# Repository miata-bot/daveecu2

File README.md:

# DaveECU2 Speeduino Mainboard

## Features

* 4 Injectors
* 4 Ignitions
* 1 each CAM and Crank input
* 1 wire Idle
* PWM boost
* AC control
* 4 additional high current outputs
* SD card for logginglogging
* [PLANNED] RTC w/ battery backup

## Schematic TODO

* Calculate R53 and R54 values for 3v3 rail
* ~~Convert all resistors in the sensor sheet to 0402~~ have to hand solder so don't want that small
* ~~Convert all capacitors in the sensor sheet to 0402~~ have to hand solder so don't want that small
* Condense common resistors into common values
* Condense common caps into common values
* ~~Find a USB-C connector~~ Replaced with USB Type B "printer" connector
* Check if Q1 and Q2 can be the same part

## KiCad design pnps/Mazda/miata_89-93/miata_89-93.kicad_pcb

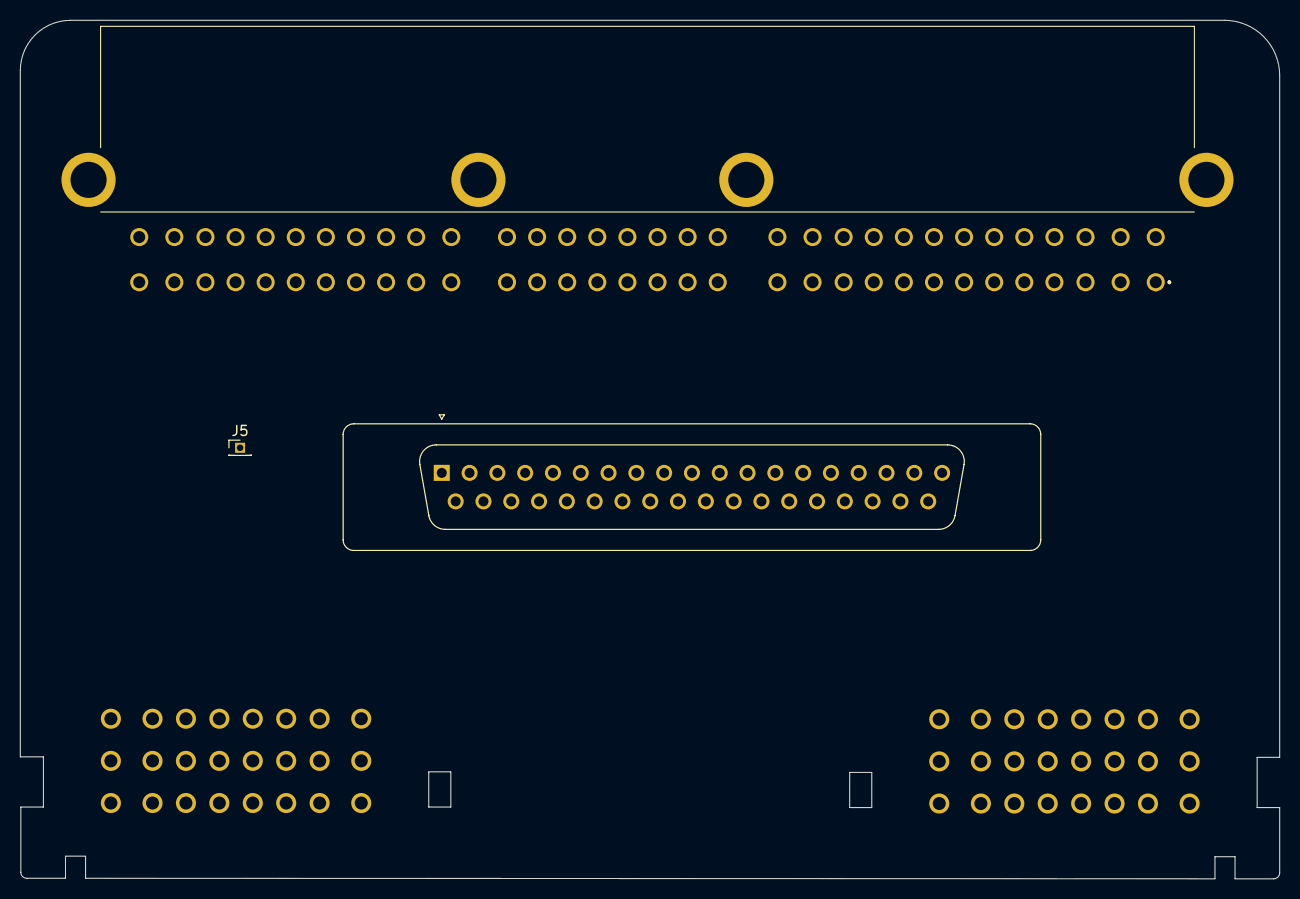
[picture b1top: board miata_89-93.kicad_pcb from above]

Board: 2 copper layers, 125.5 x 85.5 mm, 5 parts (0 on the bottom side), 24 nets.

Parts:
J1: 174518-7
J2: Conn_01x37; DSUB-37_Male_Vertical_P2.77x2.84mm
J3: CONN_BLACK; Delphi_Sicma_24_Black
J4: CONN_GRAY; Delphi_Sicma_24_Grey
J5: 2ND TRIGGER; PinHeader_1x01_P1.27mm_Vertical

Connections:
GND: J1.MH1, J1.MH2, J1.MH3, J1.MH4, J3.A1, J3.A3, J3.A4, J3.A5, J3.B1, J3.B2, J3.B3, J3.B4, J4.C1, J4.C2
MIATA_1B: J1.16, J2.28
MIATA_1E: J1.56, J4.B4
MIATA_1G: J1.55, J3.C1
MIATA_1H: J1.63, J3.C3
MIATA_1N: J1.52, J1.60, J2.26, J3.A7
MIATA_1Q: J1.50, J4.A1
MIATA_1R: J1.58, J4.C4
MIATA_1V: J1.12, J4.A2
MIATA_2A: J1.8, J2.8, J2.9
MIATA_2C: J1.7, J2.1
MIATA_2D: J1.9, J2.2
MIATA_2E: J1.24, J2.24, J4.A8
MIATA_2G: J1.23, J4.A7, J5.1
MIATA_2I: J1.22, J4.C5
MIATA_2K: J1.21, J4.B8
MIATA_2L: J1.29, J2.22, J4.A3
MIATA_2N: J1.28, J2.23
MIATA_2O: J1.19, J2.37, J4.C3
MIATA_2P: J1.27, J2.20, J4.A4
MIATA_2Q: J1.18, J2.21, J4.A5
MIATA_2U: J1.3, J3.C7
MIATA_2V: J1.6, J3.C5
MIATA_2W: J1.2, J4.B7

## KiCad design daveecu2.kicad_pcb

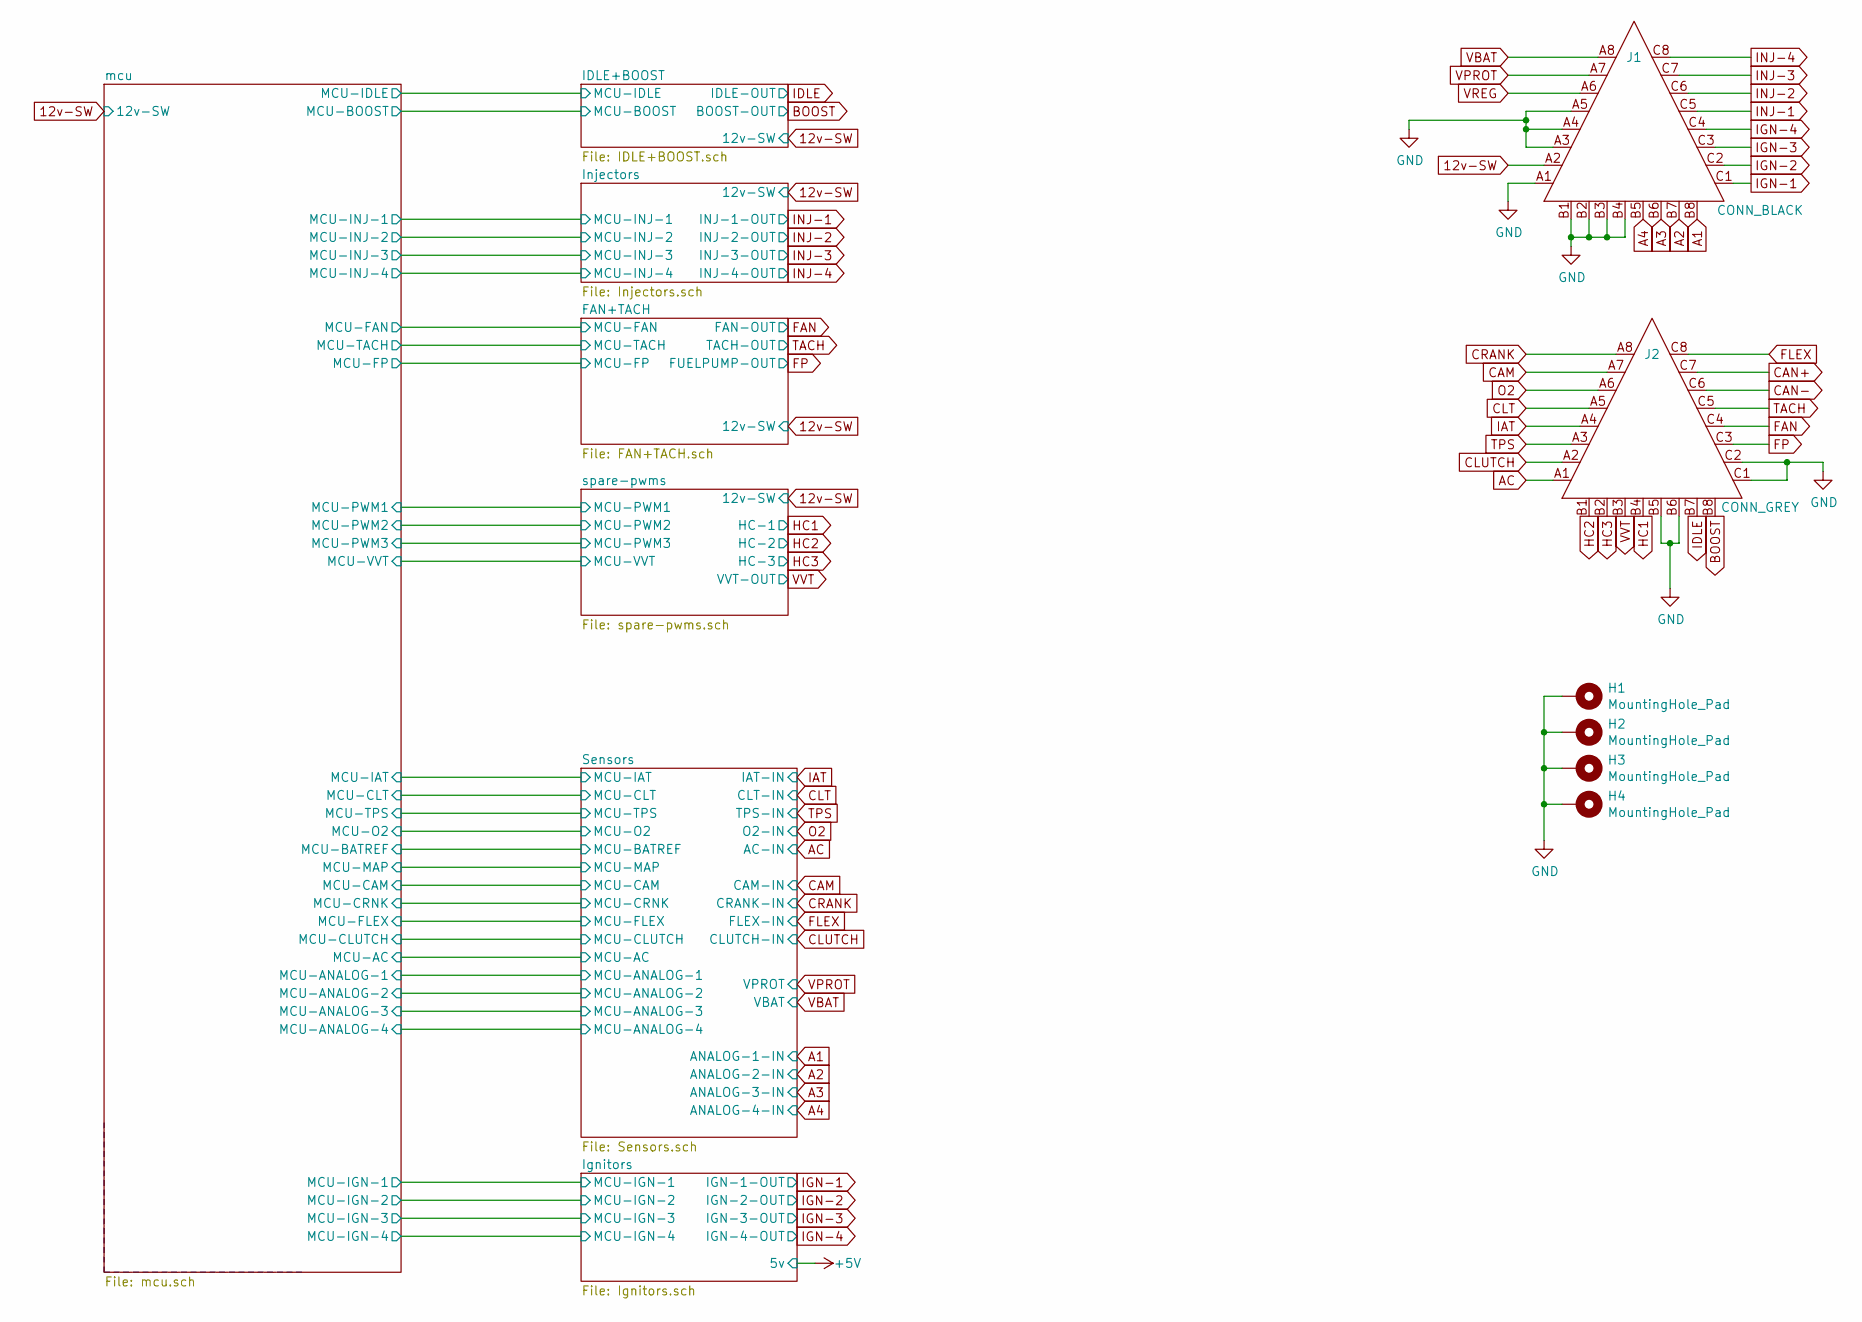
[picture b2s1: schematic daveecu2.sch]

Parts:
H1, H2, H3, H4: MountingHole_Pad; MountingHole_4.3mm_M4_Pad_Via
J1: CONN_BLACK; Delphi_Sicma_24_Black
J2: CONN_GREY; Delphi_Sicma_24_Grey

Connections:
12v-SW: J1.A2; also elsewhere on the board
A1: J1.B8; also elsewhere on the board
A2: J1.B7; also elsewhere on the board
A3: J1.B6; also elsewhere on the board
A4: J1.B5; also elsewhere on the board
AC: J2.A1; also elsewhere on the board
ADC-CLAMP-7: J2.C8; also elsewhere on the board
BOOST: J2.B8; also elsewhere on the board
CAM: J2.A7; also elsewhere on the board
CAN+: J2.C7; also elsewhere on the board
CAN-: J2.C6; also elsewhere on the board
CLT: J2.A5; also elsewhere on the board
CLUTCH: J2.A2; also elsewhere on the board
CRANK: J2.A8; also elsewhere on the board
FAN: J2.C4; also elsewhere on the board
FP: J2.C3; also elsewhere on the board
GND: H1.1, H2.1, H3.1, H4.1, J1.A1, J1.A3, J1.A4, J1.A5, J1.B1, J1.B2, J1.B3, J1.B4, J2.B5, J2.B6, J2.C1, J2.C2; also elsewhere on the board
HC1: J2.B4; also elsewhere on the board
HC2: J2.B1; also elsewhere on the board
HC3: J2.B2; also elsewhere on the board
IAT: J2.A4; also elsewhere on the board
IDLE: J2.B7; also elsewhere on the board
IGN-1: J1.C1; also elsewhere on the board
IGN-2: J1.C2; also elsewhere on the board
IGN-3: J1.C3; also elsewhere on the board
IGN-4: J1.C4; also elsewhere on the board
INJ-1: J1.C5; also elsewhere on the board
INJ-2: J1.C6; also elsewhere on the board
INJ-3: J1.C7; also elsewhere on the board
INJ-4: J1.C8; also elsewhere on the board
O2: J2.A6; also elsewhere on the board
TACH: J2.C5; also elsewhere on the board
TPS: J2.A3; also elsewhere on the board
VBAT: J1.A8; also elsewhere on the board
VPROT: J1.A7; also elsewhere on the board
VREG: J1.A6; also elsewhere on the board
VVT: J2.B3; also elsewhere on the board

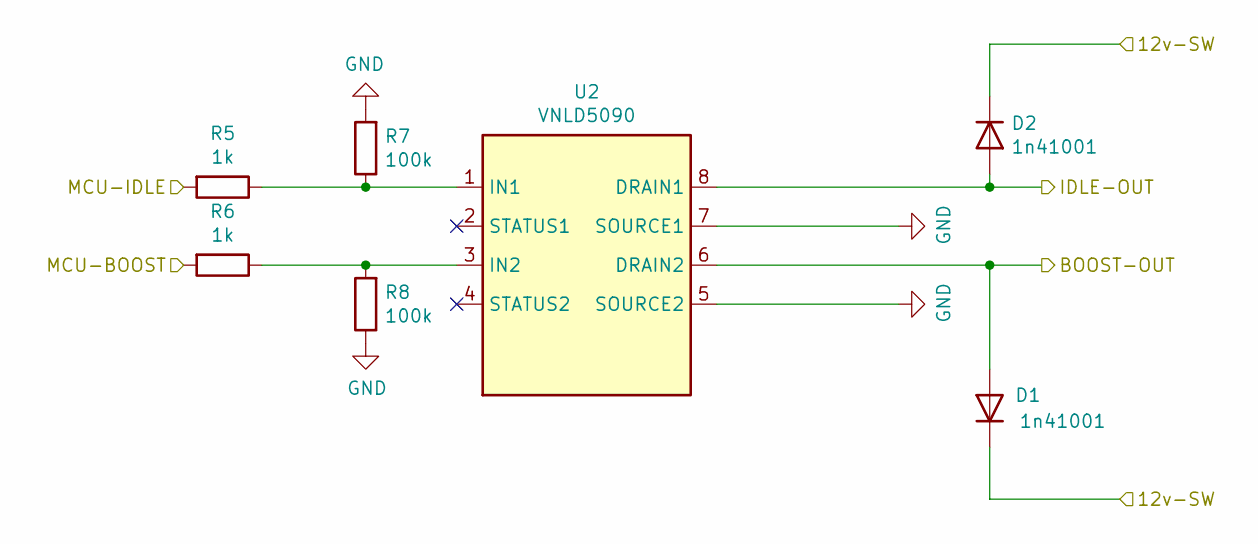
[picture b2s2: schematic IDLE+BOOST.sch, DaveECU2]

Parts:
D1, D2: 1n41001; D_SOD-123; LCSC_PN C162732
R5, R6: 1k; R_0603_1608Metric_Pad0.98x0.95mm_HandSolder; DIGIKEY 311-1.00KCRCT-ND
R7, R8: 100k; R_0603_1608Metric_Pad0.98x0.95mm_HandSolder; DIGIKEY 311-100KCRCT-ND
U2: VNLD5090; SOIC-8_3.9x4.9mm_P1.27mm

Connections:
12v-SW: D1.1 (K), D2.1 (K); also elsewhere on the board
/IDLE+BOOST/MCU-BOOST: R6.2; also elsewhere on the board
/IDLE+BOOST/MCU-IDLE: R5.2; also elsewhere on the board
BOOST: D1.2 (A), U2.6 (DRAIN2); also elsewhere on the board
GND: R7.2, R8.1, U2.5 (SOURCE2), U2.7 (SOURCE1); also elsewhere on the board
IDLE: D2.2 (A), U2.8 (DRAIN1); also elsewhere on the board
unnamed: R5.1, R7.1, U2.1 (IN1)
unnamed: R6.1, R8.2, U2.3 (IN2)

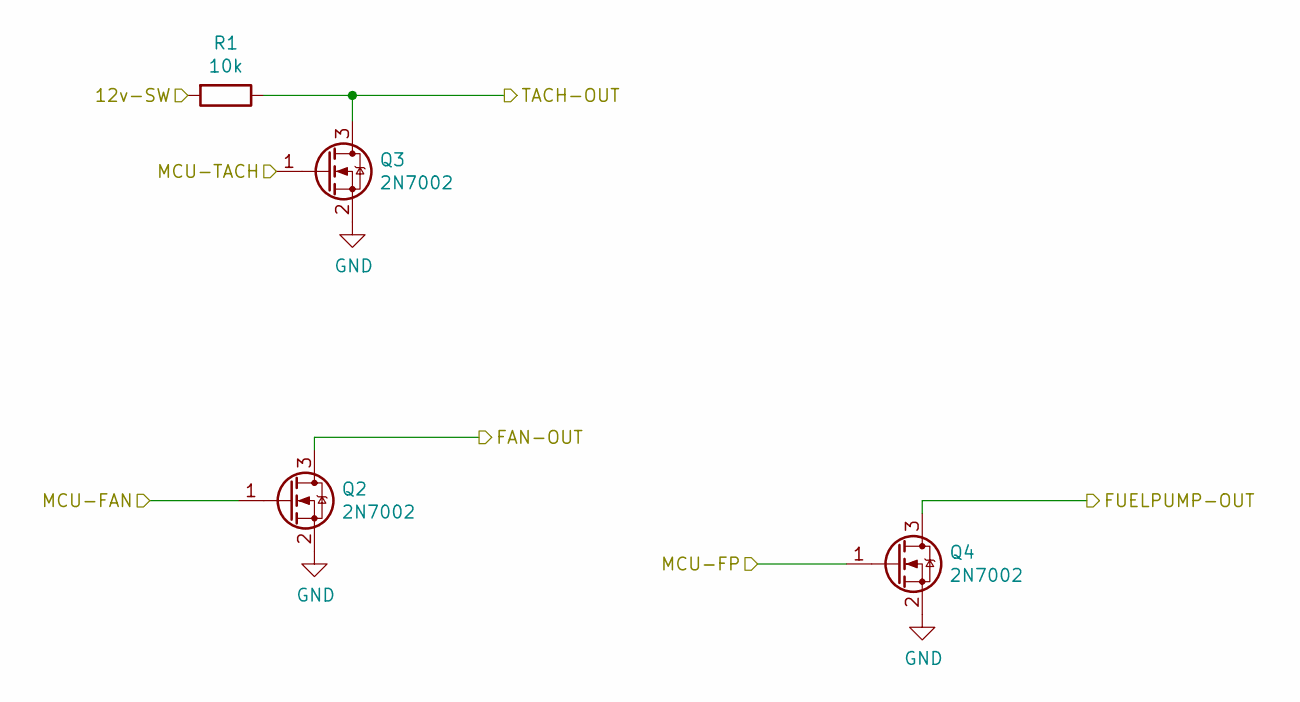
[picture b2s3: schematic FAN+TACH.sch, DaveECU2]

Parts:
Q2, Q3, Q4: 2N7002; SOT-23
R1: 10k; R_0603_1608Metric_Pad0.98x0.95mm_HandSolder; DIGIKEY 311-1.00KCRCT-ND

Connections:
12v-SW: R1.2; also elsewhere on the board
/FAN+TACH/MCU-FAN: Q2.1 (G); also elsewhere on the board
/FAN+TACH/MCU-FP: Q4.1 (G); also elsewhere on the board
/FAN+TACH/MCU-TACH: Q3.1 (G); also elsewhere on the board
FAN: Q2.3 (D); also elsewhere on the board
FP: Q4.3 (D); also elsewhere on the board
GND: Q2.2 (S), Q3.2 (S), Q4.2 (S); also elsewhere on the board
TACH: Q3.3 (D), R1.1; also elsewhere on the board

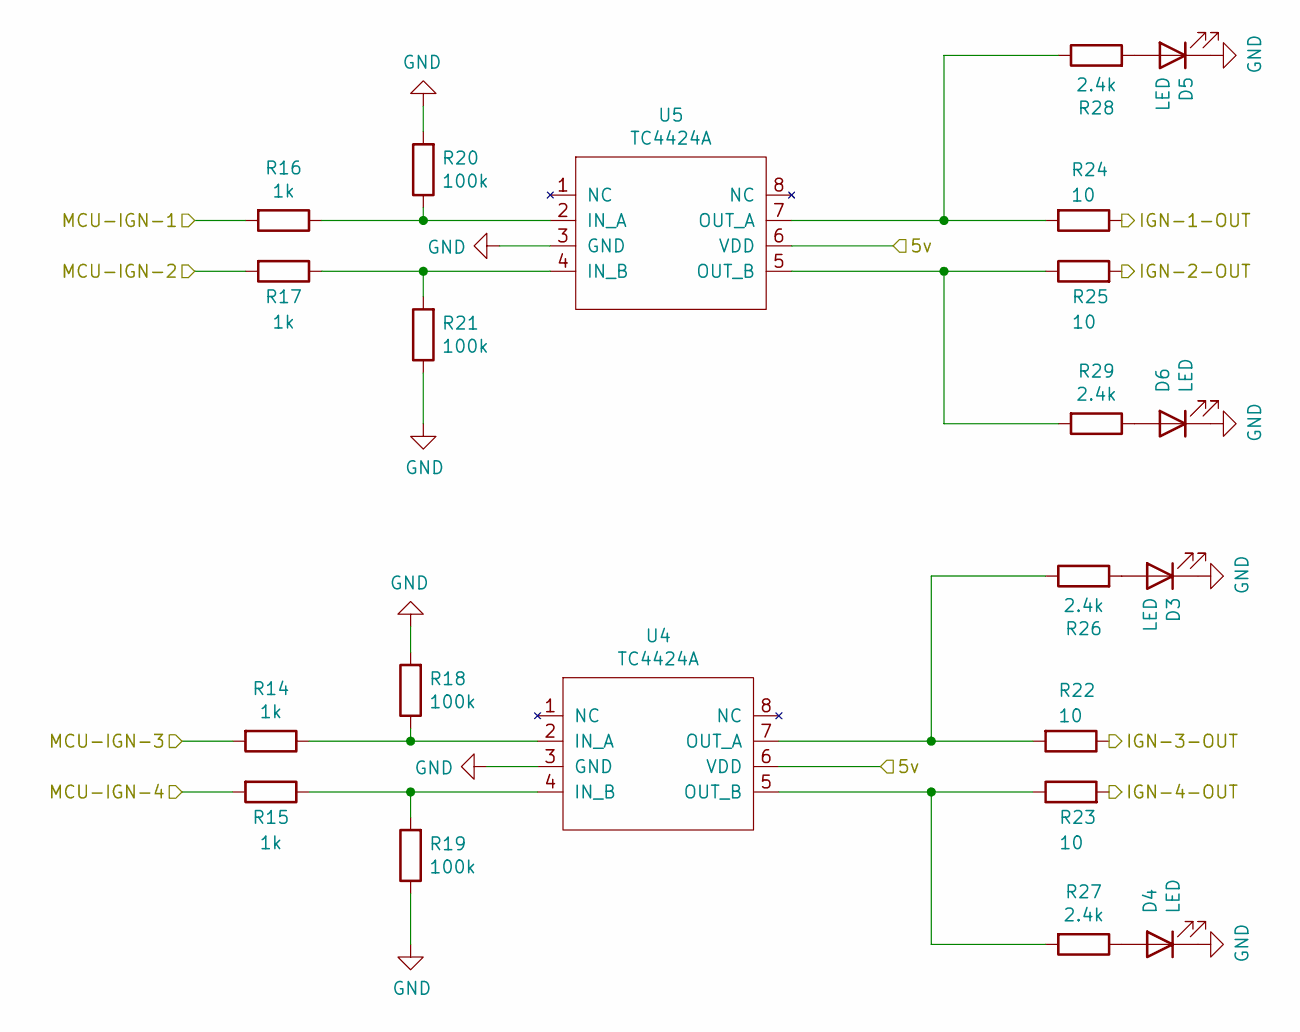
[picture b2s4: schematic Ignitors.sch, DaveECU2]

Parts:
D3, D4, D5, D6: LED; LED_0603_1608Metric_Pad1.05x0.95mm_HandSolder
R14, R15, R16, R17: 1k; R_0603_1608Metric_Pad0.98x0.95mm_HandSolder; DIGIKEY 311-1.00KCRCT-ND
R18, R19, R20, R21: 100k; R_0603_1608Metric_Pad0.98x0.95mm_HandSolder; DIGIKEY 311-100KCRCT-ND
R22, R23, R24, R25: 10; R_0603_1608Metric_Pad0.98x0.95mm_HandSolder; DIGIKEY 311-10.0CRCT-ND
R26, R27, R28, R29: 2.4k; R_0603_1608Metric_Pad0.98x0.95mm_HandSolder; DIGIKEY 311-2.40KCRCT-ND
U4, U5: TC4424A; SOIC-8_3.9x4.9mm_P1.27mm; DIGIKEY TC4424AVOA-ND

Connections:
/Ignitors/MCU-IGN-1: R16.2; also elsewhere on the board
/Ignitors/MCU-IGN-2: R17.2; also elsewhere on the board
/Ignitors/MCU-IGN-3: R14.2; also elsewhere on the board
/Ignitors/MCU-IGN-4: R15.2; also elsewhere on the board
GND: D3.1 (K), D4.1 (K), D5.1 (K), D6.1 (K), R18.2, R19.1, R20.2, R21.1, U4.3 (GND), U5.3 (GND); also elsewhere on the board
IGN-1: R24.1; also elsewhere on the board
IGN-2: R25.2; also elsewhere on the board
IGN-3: R22.1; also elsewhere on the board
IGN-4: R23.2; also elsewhere on the board
unnamed: D3.2 (A), R26.2
unnamed: D4.2 (A), R27.1
unnamed: D5.2 (A), R28.2
unnamed: D6.2 (A), R29.1
unnamed: R14.1, R18.1, U4.2 (IN_A)
unnamed: R15.1, R19.2, U4.4 (IN_B)
unnamed: R16.1, R20.1, U5.2 (IN_A)
unnamed: R17.1, R21.2, U5.4 (IN_B)
unnamed: R22.2, R26.1, U4.7 (OUT_A)
unnamed: R23.1, R27.2, U4.5 (OUT_B)
unnamed: R24.2, R28.1, U5.7 (OUT_A)
unnamed: R25.1, R29.2, U5.5 (OUT_B)
VPROT: U4.6 (VDD), U5.6 (VDD); also elsewhere on the board

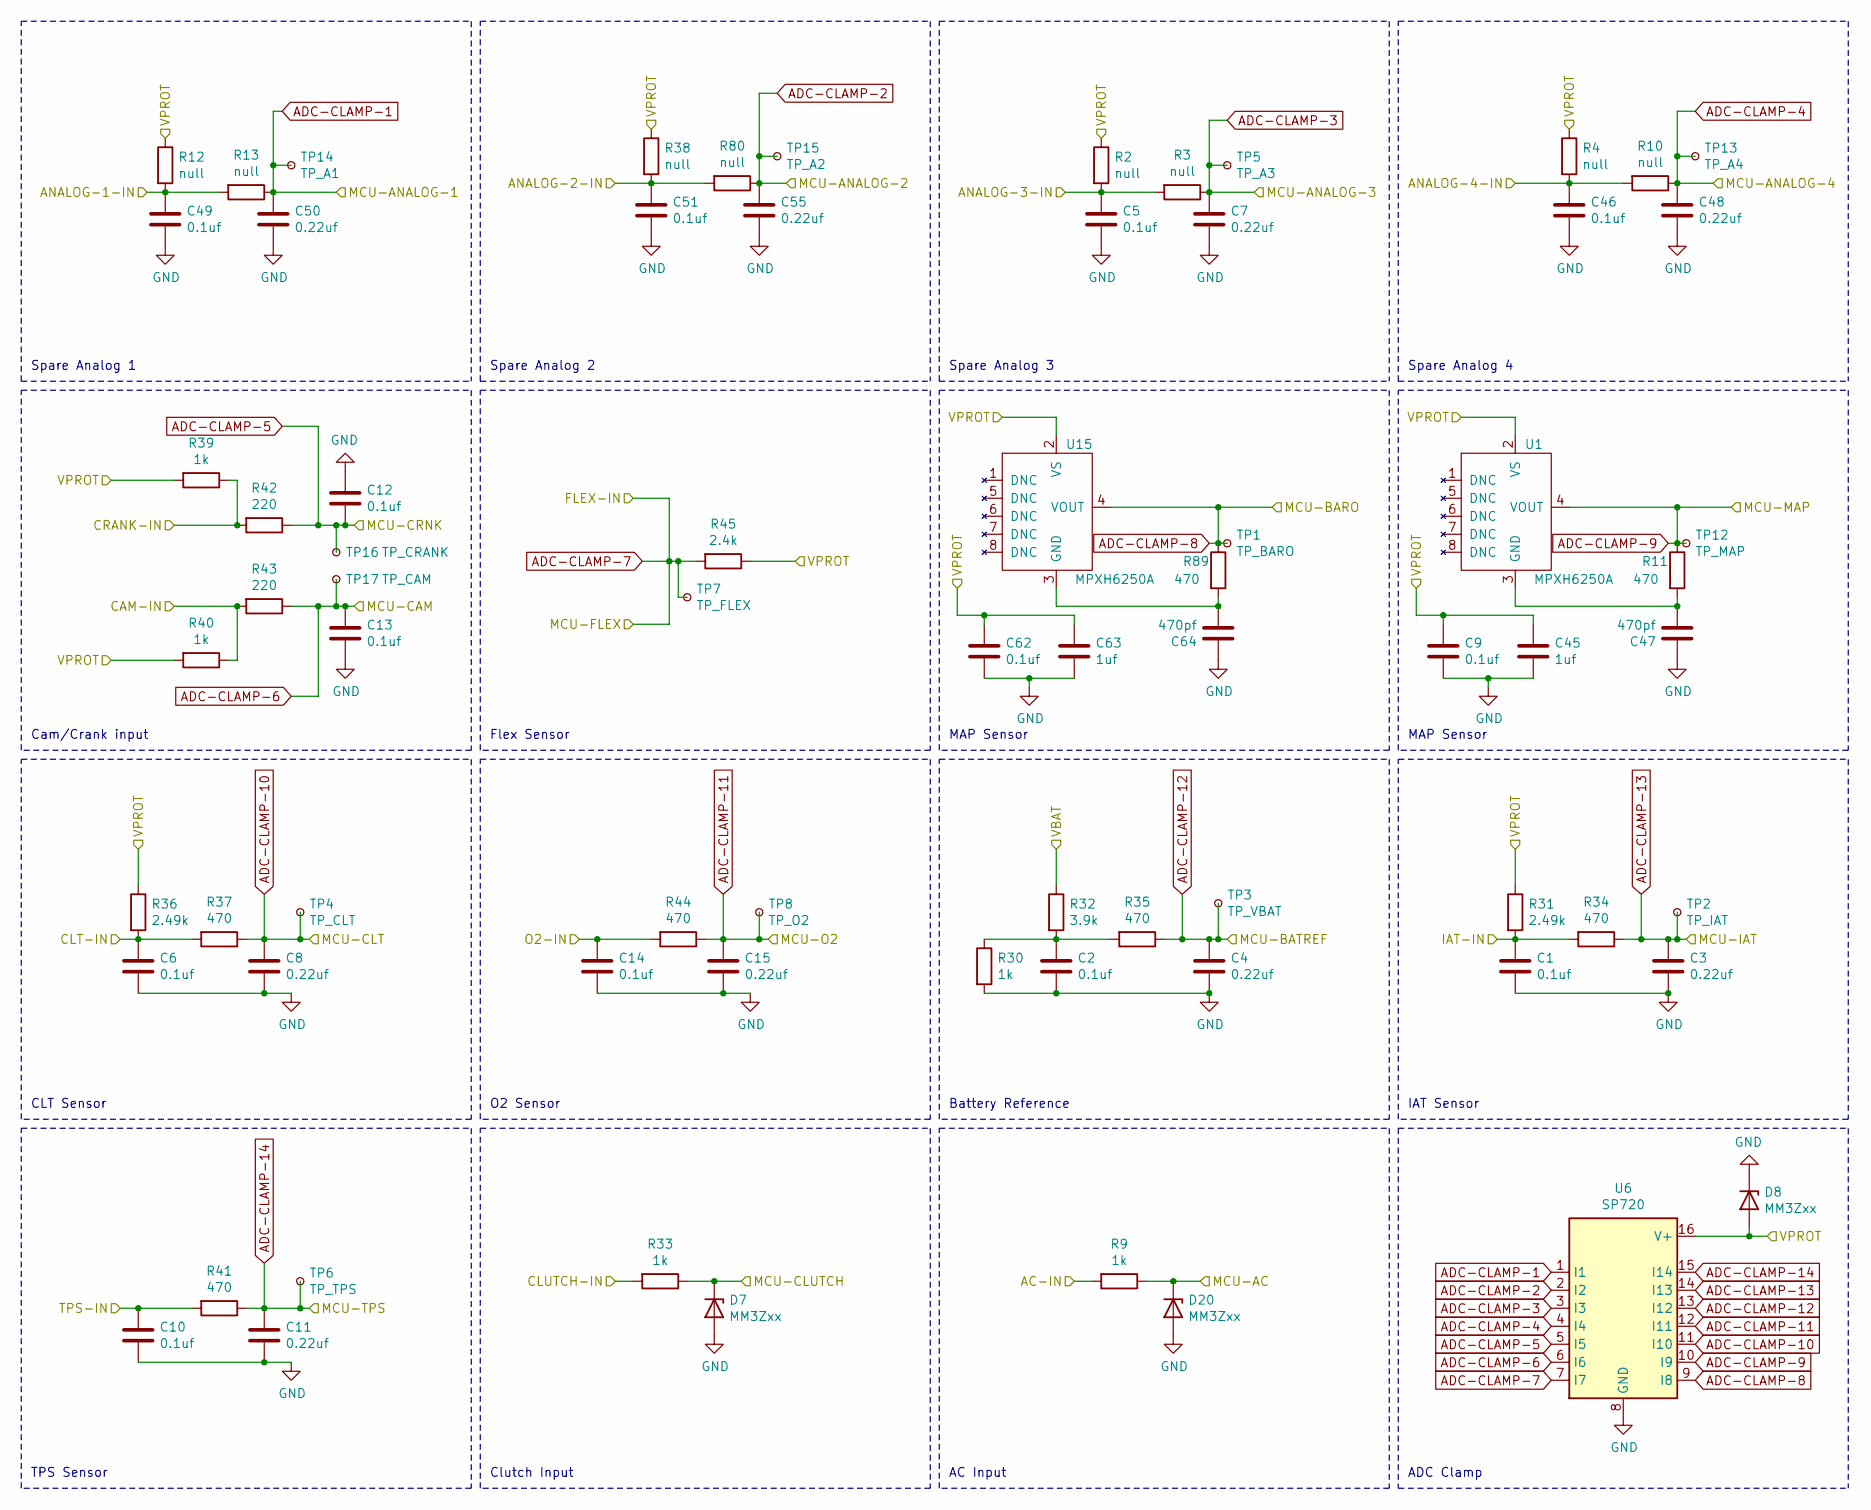
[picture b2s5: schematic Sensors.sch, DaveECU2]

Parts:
C1, C2, C5, C6, C9, C10, C12, C13, C14, C46, C49, C51, C62: 0.1uf; C_0805_2012Metric_Pad1.18x1.45mm_HandSolder; DIGIKEY 311-1140-1-ND
C3, C4, C7, C8, C11, C15, C48, C50, C55: 0.22uf; C_0805_2012Metric_Pad1.18x1.45mm_HandSolder; DIGIKEY 1276-1284-1-ND
C45, C63: 1uf; C_0805_2012Metric_Pad1.18x1.45mm_HandSolder; DIGIKEY 311-1365-1-ND
C47, C64: 470pf; C_0805_2012Metric_Pad1.18x1.45mm_HandSolder; DIGIKEY 311-1124-1-ND
D7, D8, D20: MM3Zxx; D_SOD-323_HandSoldering; DIGIKEY MM3Z5V1ST1GOSCT-ND
R2, R4, R12, R38: null; R_0805_2012Metric_Pad1.20x1.40mm_HandSolder; DIGIKEY YAG1854CT-ND
R3, R10, R13, R80: null; R_0805_2012Metric_Pad1.20x1.40mm_HandSolder; DIGIKEY P470CCT-ND
R9, R30, R33, R39, R40: 1k; R_0805_2012Metric_Pad1.20x1.40mm_HandSolder; DIGIKEY 311-1.00KCRCT-ND
R11, R34, R35, R37, R41, R44, R89: 470; R_0805_2012Metric_Pad1.20x1.40mm_HandSolder; DIGIKEY P470CCT-ND
R31, R36: 2.49k; R_0805_2012Metric_Pad1.20x1.40mm_HandSolder; DIGIKEY YAG1854CT-ND
R32: 3.9k; R_0805_2012Metric_Pad1.20x1.40mm_HandSolder; DIGIKEY 311-3.90KCRCT-ND
R42, R43: 220; R_0805_2012Metric_Pad1.20x1.40mm_HandSolder; DIGIKEY 311-220CRCT-ND
R45: 2.4k; R_0805_2012Metric_Pad1.20x1.40mm_HandSolder; DIGIKEY 311-2.40KCRCT-ND
TP1: TP_BARO; TestPoint_Pad_D1.0mm
TP2: TP_IAT; TestPoint_Pad_D1.0mm
TP3: TP_VBAT; TestPoint_Pad_D1.0mm
TP4: TP_CLT; TestPoint_Pad_D1.0mm
TP5: TP_A3; TestPoint_Pad_D1.0mm
TP6: TP_TPS; TestPoint_Pad_D1.0mm
TP7: TP_FLEX; TestPoint_Pad_D1.0mm
TP8: TP_O2; TestPoint_Pad_D1.0mm
TP12: TP_MAP; TestPoint_Pad_D1.0mm
TP13: TP_A4; TestPoint_Pad_D1.0mm
TP14: TP_A1; TestPoint_Pad_D1.0mm
TP15: TP_A2; TestPoint_Pad_D1.0mm
TP16: TP_CRANK; TestPoint_Pad_D1.0mm
TP17: TP_CAM; TestPoint_Pad_D1.0mm
U1, U15: MPXH6250A; Freescale_98ARH99066A
U6: SP720; SOIC-16_3.9x9.9mm_P1.27mm; DIGIKEY F3162CT-ND

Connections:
/Sensors/MCU-AC: D20.1 (K), R9.1; also elsewhere on the board
/Sensors/MCU-CLUTCH: D7.1 (K), R33.1; also elsewhere on the board
A1: C49.1, R12.2, R13.2; also elsewhere on the board
A2: C51.1, R38.2, R80.2; also elsewhere on the board
A3: C5.1, R2.2, R3.2; also elsewhere on the board
A4: C46.1, R4.2, R10.2; also elsewhere on the board
AC: R9.2; also elsewhere on the board
ADC-CLAMP-1: C50.1, R13.1, TP14.1, U6.1 (I1); also elsewhere on the board
ADC-CLAMP-2: C55.1, R80.1, TP15.1, U6.2 (I2); also elsewhere on the board
ADC-CLAMP-3: C7.1, R3.1, TP5.1, U6.3 (I3); also elsewhere on the board
ADC-CLAMP-4: C48.1, R10.1, TP13.1, U6.4 (I4); also elsewhere on the board
ADC-CLAMP-5: C12.2, R42.1, TP16.1, U6.5 (I5); also elsewhere on the board
ADC-CLAMP-6: C13.1, R43.1, TP17.1, U6.6 (I6); also elsewhere on the board
ADC-CLAMP-7: R45.2, TP7.1, U6.7 (I7); also elsewhere on the board
ADC-CLAMP-8: R89.1, TP1.1, U6.9 (I8), U15.4 (VOUT)
ADC-CLAMP-9: R11.1, TP12.1, U1.4 (VOUT), U6.10 (I9); also elsewhere on the board
ADC-CLAMP-10: C8.1, R37.1, TP4.1, U6.11 (I10); also elsewhere on the board
ADC-CLAMP-11: C15.1, R44.1, TP8.1, U6.12 (I11); also elsewhere on the board
ADC-CLAMP-12: C4.1, R35.1, TP3.1, U6.13 (I12); also elsewhere on the board
ADC-CLAMP-13: C3.1, R34.1, TP2.1, U6.14 (I13); also elsewhere on the board
ADC-CLAMP-14: C11.1, R41.1, TP6.1, U6.15 (I14); also elsewhere on the board
CAM: R40.1, R43.2; also elsewhere on the board
CLT: C6.1, R36.2, R37.2; also elsewhere on the board
CLUTCH: R33.2; also elsewhere on the board
CRANK: R39.1, R42.2; also elsewhere on the board
GND: C1.2, C2.2, C3.2, C4.2, C5.2, C6.2, C7.2, C8.2, C9.2, C10.2, C11.2, C12.1, C13.2, C14.2, C15.2, C45.2, C46.2, C47.1, C48.2, C49.2, C50.2, C51.2, C55.2, C62.2, C63.2, C64.1, D7.2 (A), D8.1 (K), D20.2 (A), R30.2, U6.8 (GND); also elsewhere on the board
IAT: C1.1, R31.2, R34.2; also elsewhere on the board
unnamed: C2.1, R30.1, R32.2, R35.2
unnamed: C47.2, R11.2, U1.3 (GND)
unnamed: C64.2, R89.2, U15.3 (GND)
O2: C14.1, R44.2; also elsewhere on the board
TPS: C10.1, R41.2; also elsewhere on the board
VBAT: R32.1; also elsewhere on the board
VPROT: C9.1, C45.1, C62.1, C63.1, D8.2 (A), R2.1, R4.1, R12.1, R31.1, R36.1, R38.1, R39.2, R40.2, R45.1, U1.2 (VS), U6.16 (V+), U15.2 (VS); also elsewhere on the board

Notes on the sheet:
IAT Sensor
CLT Sensor
TPS Sensor
O2 Sensor
Battery Reference
Cam/Crank input
Flex Sensor
Clutch Input
ADC Clamp
AC Input
Spare Analog 1
Spare Analog 2
Spare Analog 3
Spare Analog 4
MAP Sensor

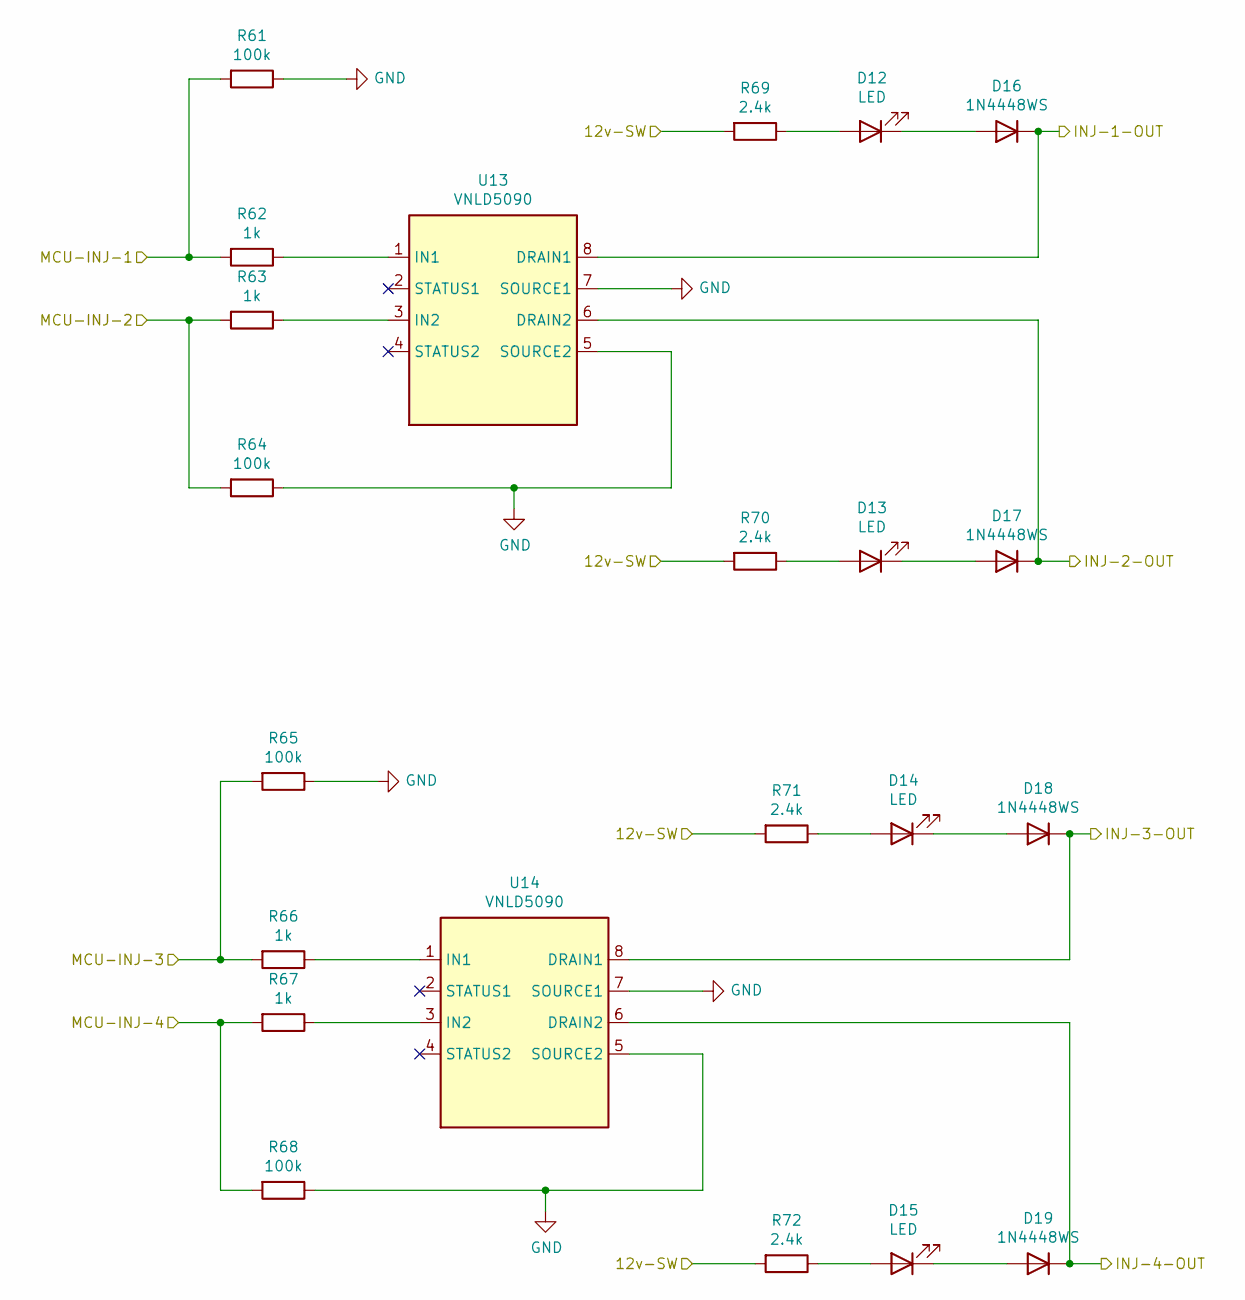
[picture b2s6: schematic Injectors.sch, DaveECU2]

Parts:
D12, D13, D14, D15: LED; LED_0603_1608Metric_Pad1.05x0.95mm_HandSolder; DIGIKEY 475-1415-1-ND
D16, D17, D18, D19: 1N4448WS; D_SOD-323_HandSoldering; DIGIKEY 1N4448WXTPMSCT-ND
R61, R64, R65, R68: 100k; R_0603_1608Metric_Pad0.98x0.95mm_HandSolder; DIGIKEY 311-100KCRCT-ND
R62, R63, R66, R67: 1k; R_0603_1608Metric_Pad0.98x0.95mm_HandSolder; DIGIKEY 311-1.00KCRCT-ND
R69, R70, R71, R72: 2.4k; R_0603_1608Metric_Pad0.98x0.95mm_HandSolder; DIGIKEY 311-2.40KCRCT-ND
U13, U14: VNLD5090; SOIC-8_3.9x4.9mm_P1.27mm; MOUSER 511-VNLD5090-E

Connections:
12v-SW: R69.2, R70.2, R71.2, R72.2; also elsewhere on the board
/Injectors/MCU-INJ-1: R61.2, R62.2; also elsewhere on the board
/Injectors/MCU-INJ-2: R63.2, R64.2; also elsewhere on the board
/Injectors/MCU-INJ-3: R65.2, R66.2; also elsewhere on the board
/Injectors/MCU-INJ-4: R67.2, R68.2; also elsewhere on the board
GND: R61.1, R64.1, R65.1, R68.1, U13.5 (SOURCE2), U13.7 (SOURCE1), U14.5 (SOURCE2), U14.7 (SOURCE1); also elsewhere on the board
INJ-1: D16.1 (K), U13.8 (DRAIN1); also elsewhere on the board
INJ-2: D17.1 (K), U13.6 (DRAIN2); also elsewhere on the board
INJ-3: D18.1 (K), U14.8 (DRAIN1); also elsewhere on the board
INJ-4: D19.1 (K), U14.6 (DRAIN2); also elsewhere on the board
unnamed: D12.1 (K), D16.2 (A)
unnamed: D12.2 (A), R69.1
unnamed: D13.1 (K), D17.2 (A)
unnamed: D13.2 (A), R70.1
unnamed: D14.1 (K), D18.2 (A)
unnamed: D14.2 (A), R71.1
unnamed: D15.1 (K), D19.2 (A)
unnamed: D15.2 (A), R72.1
unnamed: R62.1, U13.1 (IN1)
unnamed: R63.1, U13.3 (IN2)
unnamed: R66.1, U14.1 (IN1)
unnamed: R67.1, U14.3 (IN2)

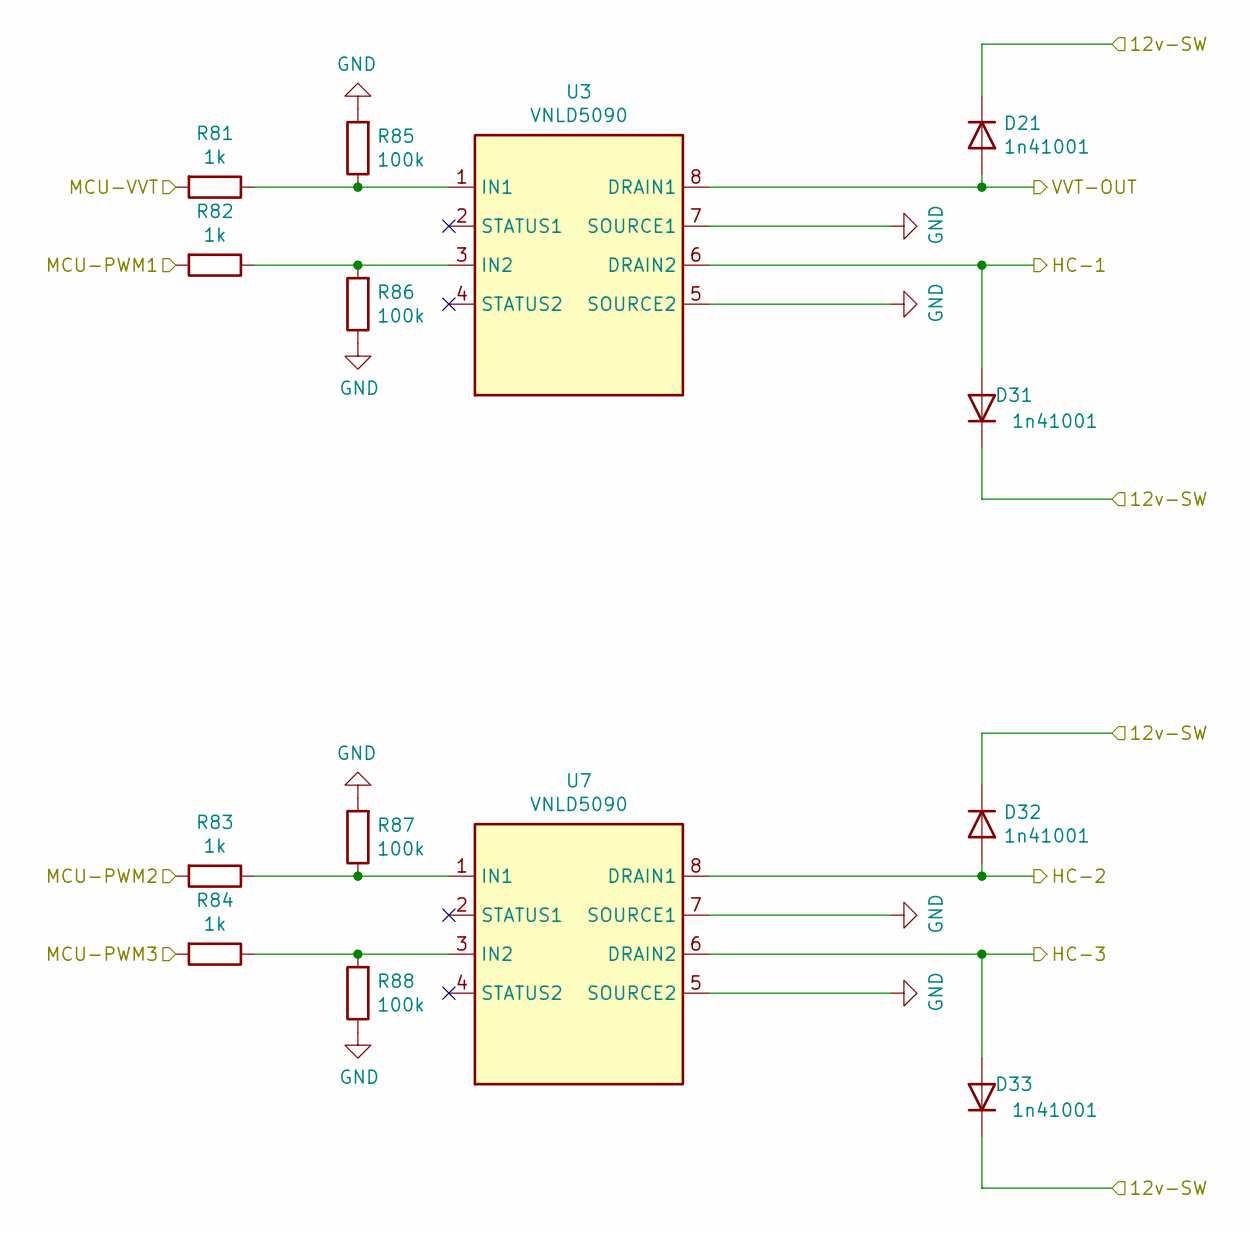
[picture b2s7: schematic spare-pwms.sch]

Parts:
D21, D31, D32, D33: 1n41001; D_SOD-123; LCSC_PN C162732
R81, R82, R83, R84: 1k; R_0603_1608Metric_Pad0.98x0.95mm_HandSolder; DIGIKEY 311-1.00KCRCT-ND
R85, R86, R87, R88: 100k; R_0603_1608Metric_Pad0.98x0.95mm_HandSolder; DIGIKEY 311-100KCRCT-ND
U3, U7: VNLD5090; SOIC-8_3.9x4.9mm_P1.27mm

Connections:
12v-SW: D21.1 (K), D31.1 (K), D32.1 (K), D33.1 (K); also elsewhere on the board
/mcu/MCU-PWM1: R82.2; also elsewhere on the board
/mcu/MCU-PWM2: R83.2; also elsewhere on the board
/mcu/MCU-PWM3: R84.2; also elsewhere on the board
/mcu/MCU-VVT: R81.2; also elsewhere on the board
GND: R85.2, R86.1, R87.2, R88.1, U3.5 (SOURCE2), U3.7 (SOURCE1), U7.5 (SOURCE2), U7.7 (SOURCE1); also elsewhere on the board
HC1: D31.2 (A), U3.6 (DRAIN2); also elsewhere on the board
HC2: D32.2 (A), U7.8 (DRAIN1); also elsewhere on the board
HC3: D33.2 (A), U7.6 (DRAIN2); also elsewhere on the board
unnamed: R81.1, R85.1, U3.1 (IN1)
unnamed: R82.1, R86.2, U3.3 (IN2)
unnamed: R83.1, R87.1, U7.1 (IN1)
unnamed: R84.1, R88.2, U7.3 (IN2)
VVT: D21.2 (A), U3.8 (DRAIN1); also elsewhere on the board

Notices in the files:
daveecu2.kicad_pcb:
daveecu2 speeduino mainboard connor rigby © 2021
